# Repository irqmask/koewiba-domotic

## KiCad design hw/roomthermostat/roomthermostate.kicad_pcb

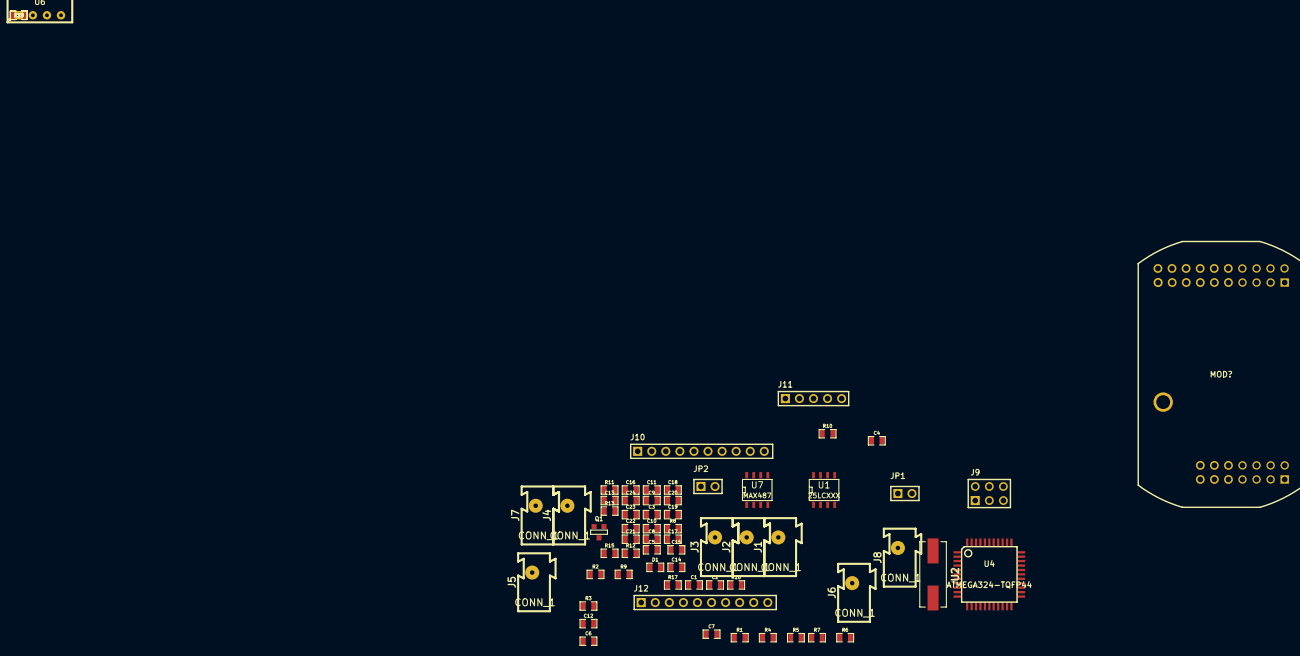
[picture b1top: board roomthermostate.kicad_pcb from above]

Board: 2 copper layers, 65 parts (0 on the bottom side), 47 nets, no tracks yet.

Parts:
C1, C2: 18pF; SM0805
C3, C4, C5, C6, C7, C15, C18, C22, C24: 100nF; SM0805
C8, C9, C10, C11, C12, C13, C16, C17: 1uF; SM0805
C14, C19, C20, C21: 4,7nF; SM0805
C23: 2,2uF; SM0805
D1: 1N4148; SM0805
J1, J2, J3, J4, J5, J6, J7, J8: CONN_1; WAGO243
J9: CONN_6X1; HEADER_3x2
J10, J12: CONN_10X1; HEADER_10x1
J11: CONN_5X1; HEADER_5x1
JP1, JP2: JUMPER; HEADER_2x1
MOD?: bus-module_atmega328
Q1: BC846; SOT23_21-3
R1, R2, R3, R5, R9, R10, R11, R12, R13: 4,7k; SM0805
R4, R6: 3,3; SM0805
R7, R8, R18, R19, R20: 1k; SM0805
R15: 120R; SM0805
R16, R17: 390R; SM0805
U1: 25LCXXX; SO8E
U2: 7,3728MHz; HC49-SMD
U4: ATMEGA324-TQFP44; TQFP44
U6: AM1S-2405; AM1S-XXXX_SIL4
U7: MAX487; SO8E

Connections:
/CS_EEP: U1.1, U4.43
/EXT_SW0: C18.1, R7.1, U4.13
/EXT_SW1: C22.1, R8.1, U4.14
/LCD_LED: R3.2, U4.16
/MISO: R19.1, U1.2
/MOSI: R18.1, U1.5
/PB0: J10.3, U4.40
/PB1: J10.4, U4.41
/PC2: J12.1, U4.21
/PC3: J12.5, U4.22
/PC4: J12.3, U4.23
/PC5: J12.9, U4.24
/PC6: J10.7, U4.25
/PC7: J10.8, U4.26
/PD3: J10.9, U4.12
/QTSCL: J10.5, U4.19
/QTSDA: J10.6, U4.20
/QTSNS0: C19.1, U4.37
/QTSNS1: C20.1, U4.35
/QTSNS2: C21.1, U4.33
/QTSNSK0: C19.2, R9.1, U4.36
/QTSNSK1: C20.2, R10.1, U4.34
/QTSNSK2: C21.2, R11.1, U4.32
/RESET: C14.1, D1.1, J9.5, JP1.1, R5.2, U4.4
/SCK: R20.1, U1.6
/businterface/Bus-A: J2.1, R15.1, R16.2, U7.6
/businterface/Bus-B: J3.1, JP2.1, R17.1, U7.7
/businterface/RXD: U4.9, U7.1
/businterface/TEN: U4.11, U7.2, U7.3
/businterface/TXD: U4.10, U7.4
GND: C1.1, C2.1, C3.2, C4.2, C5.2, C6.2, C7.2, C8.1, C9.1, C10.1, C11.1, C12.1, C13.1, C14.2, C15.2, C18.2, C22.2, C23.2, C24.2, J4.1, J6.1, J8.1, J9.6, J10.10, J12.2, J12.10, JP1.2, Q1.2, R17.2, U1.4, U4.6, U4.18, U4.28, U4.39, U6.1, U6.3, U7.5
unnamed: Q1.1, R3.1
unnamed: J5.1, R7.2, R12.2
unnamed: J7.1, R8.2, R13.2
unnamed: J11.1, R9.2
unnamed: J11.5, R11.2
unnamed: J11.3, R10.2
unnamed: C2.2, U2.2, U4.8
unnamed: C1.2, U2.1, U4.7
unnamed: C15.1, U4.29
unnamed: R1.2, U1.3
unnamed: R2.2, U1.7
unnamed: J9.1, R19.2, U4.2
unnamed: J9.4, R18.2, U4.1
unnamed: J9.3, R20.2, U4.3
unnamed: JP2.2, R15.2
VCC: C3.1, C4.1, C5.1, C6.1, C7.1, C23.1, C24.1, D1.2, J9.2, J12.4, R1.1, R2.1, R4.2, R5.1, R6.1, R12.1, R13.1, R16.1, U1.8, U4.5, U4.17, U4.38, U7.8

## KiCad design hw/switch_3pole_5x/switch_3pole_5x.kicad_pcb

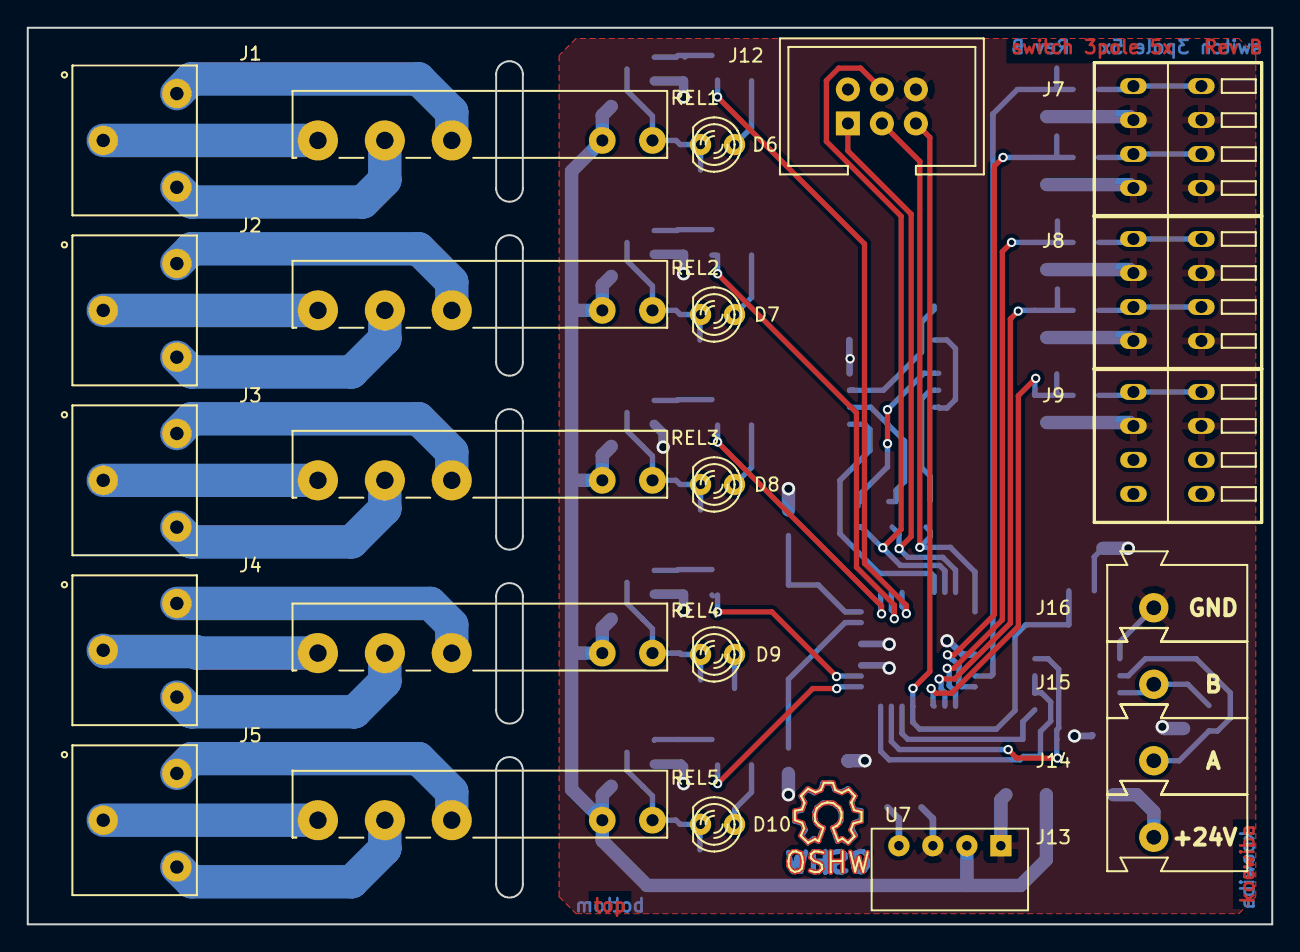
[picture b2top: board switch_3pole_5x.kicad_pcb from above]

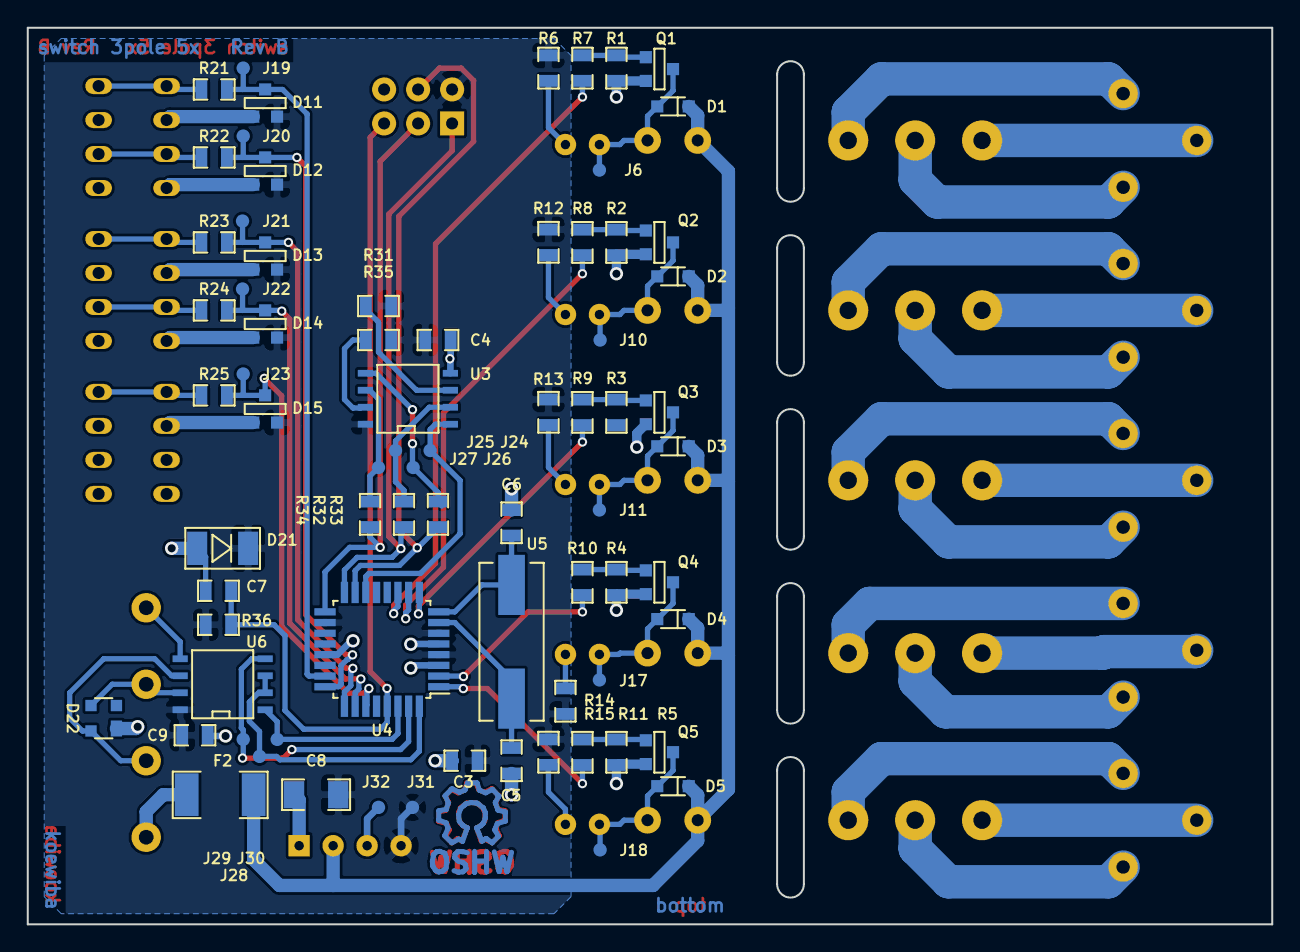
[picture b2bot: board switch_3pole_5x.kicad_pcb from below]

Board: 2 copper layers, 93.0 x 67.0 mm, 101 parts (75 on the bottom side), 66 nets.

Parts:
C3, C4, C9: 100nF; C_0805
C5, C6: 18pF; C_0805
C7: 4,7nF; C_0805
C8: 100µF / 6V; C_1206
D1, D2, D3, D4, D5: 1N4148; D_SOD323
D6, D7, D8, D9, D10: green, 2,2V/2mA; LED_RM2.54mm_D3mm
D11, D12, D13, D14, D15: BAT54S; SOT23-3
D21: ZD; D_MINIMELF
D22: SEMTECH SR05; D_SOT143
F2: FUSE; R_1812
J1, J2, J3, J4, J5: WAGO 2081-1123; WAGO2081-1123
J6: tp_relay_0; Testpoint_1mm
J7, J8: WAGO 233-504; WAGO233-4
J9: WAGO 233-502; WAGO233-4
J10: tp_relay_1; Testpoint_1mm
J11: tp_relay_2; Testpoint_1mm
J12: CONN-ISP-6; HEADER_6
J13: WAGO 243-723; WAGO243
J14: WAGO 243-724; WAGO243
J15: WAGO 243-721; WAGO243
J16: WAGO 243-722; WAGO243
J17: tp_relay_3; Testpoint_1mm
J18: tp_relay_4; Testpoint_1mm
J19: tp_button_0; Testpoint_1mm
J20: tp_button_1; Testpoint_1mm
J21: tp_button_2; Testpoint_1mm
J22: tp_button_3; Testpoint_1mm
J23: tp_button_4; Testpoint_1mm
J24: tp_cseep; Testpoint_1mm
J25: tp_miso; Testpoint_1mm
J26: tp_mosi; Testpoint_1mm
J27: tp_sck; Testpoint_1mm
J28: tp_txden; Testpoint_1mm
J29: tp_txd; Testpoint_1mm
J30: tp_rxd; Testpoint_1mm
J31: tp_vcc; Testpoint_1mm
J32: tp_gnd; Testpoint_1mm
LOGO1, LOGO2: OPEN_HARDWARE_1; Symbol_OSHW-Logo_Copper
LOGO4: Open Hardware; Symbol_OSHW-Logo_SilkScreen
Q1, Q2, Q3, Q4, Q5: BSS138; SOT23-3
R1, R2, R3, R4, R5, R31, R35, R36: 10k; R_0805
R6, R12, R13, R14, R15: 1k5; R_0805
R7, R8, R9, R10, R11, R32, R33, R34: 100; R_0805
R21, R22, R23, R24, R25: 4k7; R_0805
REL1, REL2, REL3, REL4, REL5: FINDER_34.51.7.024; finder_34.51_1xUM
U3: 25LC256; SO8N
U4: ATMEGA328-TQFP32; TQFP-32_7x7mm_Pitch0.8mm
U5: 7,3728MHz; CRY_HC49_SMD
U6: MAX487ECSA; SO8N
U7: AM1S-2405; AM1S-XXXX_SIL4

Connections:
+5V: C3.1, C4.1, C8.1, C9.2, D11.2, D12.2, D13.2, D14.2, D15.2, D21.2, J12.2, J31.1, R6.2, R12.2, R13.2, R14.2, R15.2, R31.1, R35.1, R36.1, U3.8, U4.4, U4.6, U4.18, U6.8, U7.4
+24V: D1.2, D2.2, D3.2, D4.2, D5.2, F2.1, REL1.2, REL2.2, REL3.2, REL4.2, REL5.2, U7.2
//button_0: D11.3, J19.1, R21.1, U4.23
//button_1: D12.3, J20.1, R22.1, U4.24
//button_2: D13.3, J21.1, R23.1, U4.25
//button_3: D14.3, J22.1, R24.1, U4.26
//button_4: D15.3, J23.1, R25.1, U4.27
/Relays/RELAY_0_COM: J1.3, REL1.4
/Relays/RELAY_0_NC: J1.1, REL1.3
/Relays/RELAY_0_NO: J1.2, REL1.5
/Relays/RELAY_1_COM: J2.3, REL2.4
/Relays/RELAY_1_NC: J2.1, REL2.3
/Relays/RELAY_1_NO: J2.2, REL2.5
/Relays/RELAY_2_COM: J3.3, REL3.4
/Relays/RELAY_2_NC: J3.1, REL3.3
/Relays/RELAY_2_NO: J3.2, REL3.5
/Relays/RELAY_3_COM: J4.3, REL4.4
/Relays/RELAY_3_NC: J4.1, REL4.3
/Relays/RELAY_3_NO: J4.2, REL4.5
/Relays/RELAY_4_COM: J5.3, REL5.4
/Relays/RELAY_4_NC: J5.1, REL5.3
/Relays/RELAY_4_NO: J5.2, REL5.5
/bus_atmega328_basic//CSEEP: J24.1, U3.1, U4.14
/bus_atmega328_basic//RESET: C7.1, J12.5, R36.2, U4.29
/bus_atmega328_basic/A: D22.4, J14.1, U6.6
/bus_atmega328_basic/B: D22.3, J15.1, U6.7
/bus_atmega328_basic/MISO: J25.1, R32.2, U3.2
/bus_atmega328_basic/MOSI: J26.1, R33.2, U3.5
/bus_atmega328_basic/PB3_MOSI: J12.4, R33.1, U4.15
/bus_atmega328_basic/PB4_MISO: J12.1, R32.1, U4.16
/bus_atmega328_basic/PB5_SCK: J12.3, R34.1, U4.17
/bus_atmega328_basic/RXD0: J30.1, U4.30, U6.1
/bus_atmega328_basic/SCK: J27.1, R34.2, U3.6
/bus_atmega328_basic/TXD0: J29.1, U4.31, U6.4
/bus_atmega328_basic/TXD0EN: J28.1, U4.32, U6.2, U6.3
/relay_0: R7.2, U4.11
/relay_1: R8.2, U4.10
/relay_2: R9.2, U4.9
/relay_3: R10.2, U4.2
/relay_4: R11.2, U4.1
GND: C3.2, C4.2, C5.2, C6.2, C7.2, C8.2, C9.1, D11.1, D12.1, D13.1, D14.1, D15.1, D21.1, D22.1, J7.2, J7.4, J8.2, J8.4, J9.2, J12.6, J16.1, J32.1, Q1.2, Q2.2, Q3.2, Q4.2, Q5.2, R1.2, R2.2, R4.2, R5.2, U3.4, U4.3, U4.5, U4.21, U6.5, U7.1, U7.3
unnamed: C5.1, U4.7, U5.1
unnamed: C6.1, U4.8, U5.2
unnamed: D1.1, D6.2, J6.1, Q1.3, REL1.1
unnamed: D2.1, D7.2, J10.1, Q2.3, REL2.1
unnamed: D3.1, D8.2, J11.1, Q3.3, REL3.1
unnamed: D4.1, D9.2, J17.1, Q4.3, REL4.1
unnamed: D6.1, R6.1
unnamed: D7.1, R12.1
unnamed: D8.1, R13.1
unnamed: D9.1, R14.1
unnamed: D10.1, R15.1
unnamed: D5.1, D10.2, J18.1, Q5.3, REL5.1
unnamed: F2.2, J13.1
unnamed: J7.1, R21.2
unnamed: J7.3, R22.2
unnamed: J8.1, R23.2
unnamed: J8.3, R24.2
unnamed: J9.1, R25.2
unnamed: Q1.1, R1.1, R7.1
unnamed: Q2.1, R2.1, R8.1
unnamed: Q3.1, R3.1, R9.1
unnamed: Q4.1, R4.1, R10.1
unnamed: Q5.1, R5.1, R11.1
unnamed: R31.2, U3.3
unnamed: R35.2, U3.7

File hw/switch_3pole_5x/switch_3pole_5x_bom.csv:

"Id";"Bezeichner";"Gehäuse";"Stückzahl";"Bezeichnung";"Anbieter und Ref";
1;"U7";"AM1S-XXXX_SIL4";1;"AM1S-2405";;;
2;"REL5,REL1,REL2,REL3,REL4";"finder_34.51_1xUM";5;"FINDER_34.51.7.024";;;
3;"D6,D7,D8,D9,D10";"LED_RM2.54mm_D3mm";5;"green, 2,2V/2mA";;;
4;"J16";"WAGO243";1;"WAGO 243-722";;;
5;"J13";"WAGO243";1;"WAGO 243-723";;;
6;"J14";"WAGO243";1;"WAGO 243-724";;;
7;"J15";"WAGO243";1;"WAGO 243-721";;;
8;"J12";"HEADER_6";1;"CONN-ISP-6";;;
9;"U3";"SO8N";1;"25LC256";;;
10;"U6";"SO8N";1;"MAX487ECSA";;;
11;"D11,D12,D13,D14,D15";"SOT23-3";5;"BAT54S";;;
12;"D22";"D_SOT143";1;"SEMTECH SR05";;;
13;"F2";"R_1812";1;"FUSE";;;
14;"J7,J8";"WAGO233-4";2;"WAGO 233-504";;;
15;"J9";"WAGO233-4";1;"WAGO 233-502";;;
16;"LOGO1,LOGO2";"Symbol_OSHW-Logo_Copper";2;"OPEN_HARDWARE_1";;;
17;"LOGO4";"Symbol_OSHW-Logo_SilkScreen";1;"Open Hardware";;;
18;"Q1,Q2,Q3,Q4,Q5";"SOT23-3";5;"BSS138";;;
19;"C3,C4,C9";"C_0805";3;"100nF";;;
20;"C5,C6";"C_0805";2;"18pF";;;
21;"C7";"C_0805";1;"4,7nF";;;
22;"C8";"C_1206";1;"100µF / 6V";;;
23;"D1,D2,D3,D4,D5";"D_SOD323";5;"1N4148";;;
24;"D21";"D_MINIMELF";1;"ZD";;;
25;"R1,R2,R3,R4,R5,R31,R35,R36";"R_0805";8;"10k";;;
26;"R7,R8,R9,R10,R11,R32,R33,R34";"R_0805";8;"100";;;
27;"R21,R22,R23,R24,R25";"R_0805";5;"4k7";;;
28;"U5";"CRY_HC49_SMD";1;"7,3728MHz";;;
29;"U4";"TQFP-44_10x10mm_Pitch0.8mm";1;"ATMEGA328-TQFP32";;;
30;"J1,J2,J3,J4,J5";"WAGO2081-1123";5;"WAGO 2081-1123";;;
31;"J6";"Testpoint_1mm";1;"tp_relay_0";;;
32;"J10";"Testpoint_1mm";1;"tp_relay_1";;;
33;"J11";"Testpoint_1mm";1;"tp_relay_2";;;
34;"J17";"Testpoint_1mm";1;"tp_relay_3";;;
35;"J18";"Testpoint_1mm";1;"tp_relay_4";;;
36;"J19";"Testpoint_1mm";1;"tp_button_0";;;
37;"J20";"Testpoint_1mm";1;"tp_button_1";;;
38;"J21";"Testpoint_1mm";1;"tp_button_2";;;
39;"J22";"Testpoint_1mm";1;"tp_button_3";;;
40;"J23";"Testpoint_1mm";1;"tp_button_4";;;
41;"J24";"Testpoint_1mm";1;"tp_cseep";;;
42;"J25";"Testpoint_1mm";1;"tp_miso";;;
43;"J26";"Testpoint_1mm";1;"tp_mosi";;;
44;"J27";"Testpoint_1mm";1;"tp_sck";;;
45;"J28";"Testpoint_1mm";1;"tp_txden";;;
46;"J29";"Testpoint_1mm";1;"tp_txd";;;
47;"J30";"Testpoint_1mm";1;"tp_rxd";;;
48;"J31";"Testpoint_1mm";1;"tp_vcc";;;
49;"J32";"Testpoint_1mm";1;"tp_gnd";;;
50;"R6,R12,R13,R14,R15";"R_0805";5;"1k5";;;
